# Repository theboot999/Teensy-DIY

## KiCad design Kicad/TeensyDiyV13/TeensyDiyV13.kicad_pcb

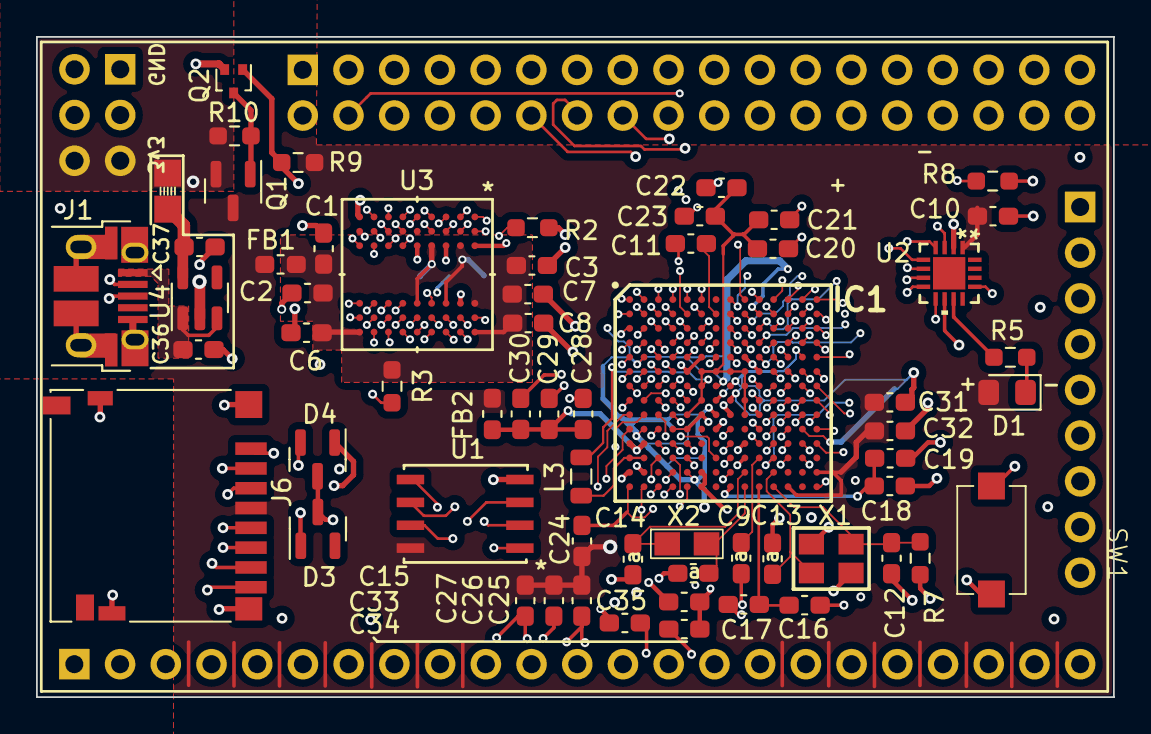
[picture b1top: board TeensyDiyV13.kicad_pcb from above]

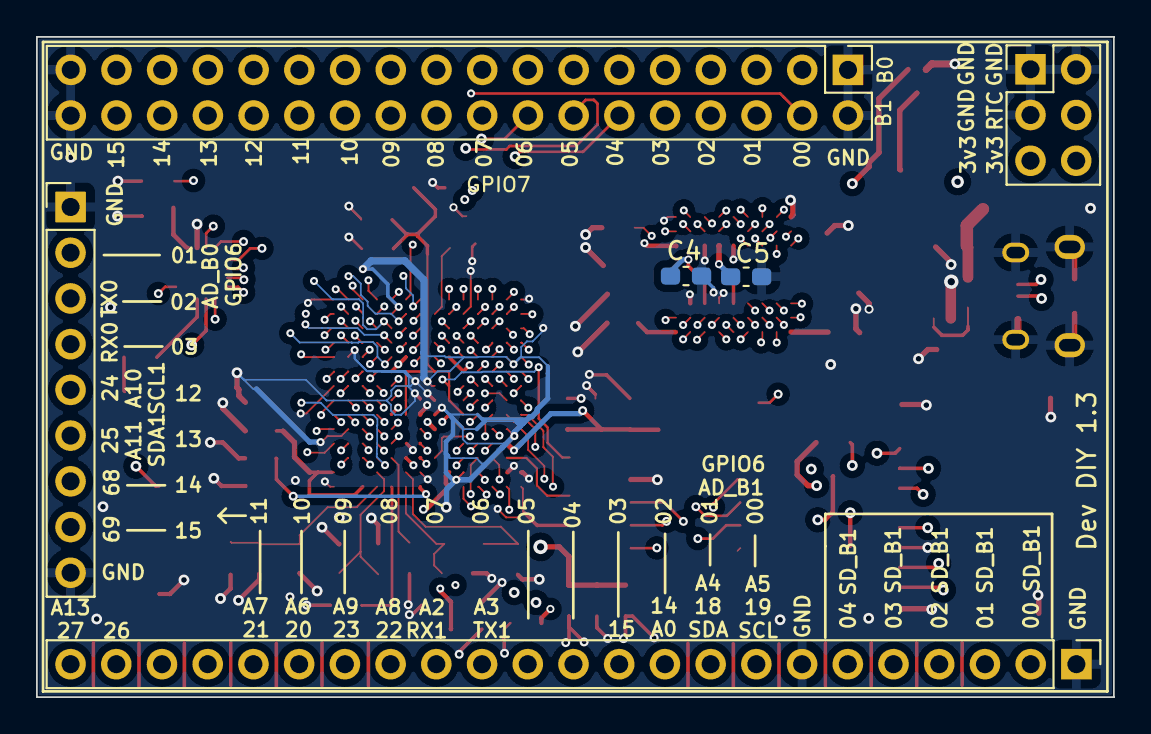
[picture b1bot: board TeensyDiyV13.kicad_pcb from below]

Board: 4 copper layers, 59.8 x 36.7 mm, 67 parts (6 on the bottom side), 146 nets.

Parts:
C1, C2, C3, C4, C5, C6, C7, C8, C9, C10, C11, C12, C13, C14, C15, C16, C17, C18, C19, C20, C21, C22, C23, C24, C25, C26, C27, C28, C29, C30, C31, C32, C33, C34, C35, C36, C37: C; C_0603_1608Metric_Pad1.08x0.95mm_HandSolder
D1: LED; LED_0805_2012Metric_Pad1.15x1.40mm_HandSolder
D3, D4: BAT54C; SOT-23
FB1, FB2: FerriteBead; L_0603_1608Metric_Pad1.05x0.95mm_HandSolder
IC1: MIMXRT1062DVJ6B; BGA196C80P14X14_1200X1200X152
J1: USB_B_Micro; USB_Micro-B_Amphenol_10103594-0001LF_Horizontal
J2: Conn_01x23; PinHeader_1x23_P2.54mm_Vertical
J3: Conn_02x18_Odd_Even; PinHeader_2x18_P2.54mm_Vertical
J4: Conn_01x08; PinHeader_1x09_P2.54mm_Vertical
J6: Micro_SD_Card_Det_Hirose_DM3AT; microSD_HC_Hirose_DM3D-SF
J7: Conn_02x04_Odd_Even; PinHeader_2x03_P2.54mm_Vertical
L3: L; L_0805_2012Metric
Q1: DMG2305UXQ; SOT-23
Q2: RE1C002UNTCL; SOT-416
R2, R3, R5, R7, R8, R9, R10: R; R_0603_1608Metric_Pad0.98x0.95mm_HandSolder
SW1: SW_Push; PTS636Button
U1: W25Q128JVPIM; Smaller_SOIC_128JVPIM_WIN
U2: MKL02Z32VFG4; QFN-16_3X3X0.65_NXP
U3: IS42S16160J-6BLI; TFBGA-54_8X8_ISI
U4: AP2112K-3.3; SOT-23-5
U5: Bridge
X1: TSX-3225
X2: Q13FC1350000400; XTAL_FC-135_EPS

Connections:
/3v3Vin: D4.1, IC1.N6 (USB_OTG1_VBUS), IC1.P6 (USB_OTG2_VBUS), J7.5, J7.6, Q1.2 (S), R10.2, U5.2 (OUT)
/3v3_Controlled: C10.2, C24.1, C25.1, C26.1, C27.1, C31.1, C32.1, D1.2 (A), FB1.2, FB2.1, IC1.E6 (NVCC_EMC_1), IC1.E9 (NVCC_GPIO_1), IC1.F5 (NVCC_EMC_2), IC1.F10 (NVCC_GPIO_2), IC1.J6 (NVCC_SD0), IC1.J10 (NVCC_GPIO_3), IC1.K4 (DCDC__IN_Q), IC1.K5 (NVCC_SD1), IC1.N14 (VDDA_ADC_3P3), IC1.P12 (VDD_HIGH_IN), J6.4 (VDD), Q1.3 (D), R9.2, U1.8 (VCC), U2.1 (VDD)
/AD_B0_01: IC1.H10 (GPIO_AD_B0_01), J4.2
/AD_B0_02: IC1.M11 (*GPIO_AD_B0_02), J4.3
/AD_B0_03: IC1.G11 (*GPIO_AD_B0_03), J4.4
/AD_B0_04: IC1.F11 (GPIO_AD_B0_04), U2.4 (PTA4)
/AD_B0_06: IC1.E14 (GPIO_AD_B0_06), U2.5 (PTA5)
/AD_B0_07: IC1.F12 (GPIO_AD_B0_07), U2.8 (PTB0)
/AD_B0_08: IC1.F13 (GPIO_AD_B0_08), U2.13 (PTB5)
/AD_B0_09: IC1.F14 (GPIO_AD_B0_09), U2.7 (PTA7)
/AD_B0_10: IC1.G13 (GPIO_AD_B0_10), U2.6 (PTA6)
/AD_B0_12: IC1.K14 (*GPIO_AD_B0_12), J4.5
/AD_B0_13: IC1.L14 (*GPIO_AD_B0_13), J4.6
/AD_B0_14: IC1.H14 (*GPIO_AD_B0_14), J4.7
/AD_B0_15: IC1.L10 (*GPIO_AD_B0_15), J4.8
/AD_B1_00: IC1.J11 (*GPIO_AD_B1_00), J2.8
/AD_B1_01: IC1.K11 (*GPIO_AD_B1_01), J2.9
/AD_B1_02: IC1.L11 (*GPIO_AD_B1_02), J2.10
/AD_B1_03: IC1.M12 (*GPIO_AD_B1_03), J2.11
/AD_B1_04: IC1.L12 (*GPIO_AD_B1_04), J2.12
/AD_B1_05: IC1.K12 (*GPIO_AD_B1_05), J2.13
/AD_B1_06: IC1.J12 (*GPIO_AD_B1_06), J2.14
/AD_B1_07: IC1.K10 (*GPIO_AD_B1_07), J2.15
/AD_B1_08: IC1.H13 (*GPIO_AD_B1_08), J2.16
/AD_B1_09: IC1.M13 (*GPIO_AD_B1_09), J2.17
/AD_B1_10: IC1.L13 (*GPIO_AD_B1_10), J2.18
/AD_B1_11: IC1.J13 (*GPIO_AD_B1_11), J2.19
/AD_B1_12: IC1.H12 (*GPIO_AD_B1_12), J2.20
/AD_B1_13: IC1.H11 (*GPIO_AD_B1_13), J2.21
/AD_B1_14: IC1.G12 (*GPIO_AD_B1_14), J2.22
/AD_B1_15: IC1.J14 (*GPIO_AD_B1_15), J2.23
/B0_00: IC1.D7 (GPIO_B0_00), J3.3
/B0_01: IC1.E7 (GPIO_B0_01), J3.5
/B0_02: IC1.E8 (GPIO_B0_02), J3.7
/B0_03: IC1.D8 (GPIO_B0_03), J3.9
/B0_04: IC1.C8 (GPIO_B0_04), J3.11
/B0_05: IC1.B8 (GPIO_B0_05), J3.13
/B0_06: IC1.A8 (GPIO_B0_06), J3.15
/B0_07: IC1.A9 (GPIO_B0_07), J3.17
/B0_08: IC1.B9 (GPIO_B0_08), J3.19
/B0_09: IC1.C9 (GPIO_B0_09), J3.21
/B0_10: IC1.D9 (GPIO_B0_10), J3.23
/B0_11: IC1.A10 (GPIO_B0_11), J3.25
/B0_12: IC1.C10 (GPIO_B0_12), J3.27
/B0_13: IC1.D10 (GPIO_B0_13), J3.29
/B0_14: IC1.E10 (GPIO_B0_14), J3.31
/B0_15: IC1.E11 (GPIO_B0_15), J3.33
/B1_00: IC1.A11 (GPIO_B1_00), J3.4
/B1_01: IC1.B11 (GPIO_B1_01), J3.6
/B1_02: IC1.C11 (GPIO_B1_02), J3.8
/B1_03: IC1.D11 (GPIO_B1_03), J3.10
/B1_04: IC1.E12 (GPIO_B1_04), J3.12
/B1_05: IC1.D12 (GPIO_B1_05), J3.14
/B1_06: IC1.C12 (GPIO_B1_06), J3.16
/B1_07: IC1.B12 (GPIO_B1_07), J3.18
/B1_08: IC1.A12 (GPIO_B1_08), J3.20
/B1_09: IC1.A13 (GPIO_B1_09), J3.22
/B1_10: IC1.B13 (GPIO_B1_10), J3.24
/B1_11: IC1.C13 (GPIO_B1_11), J3.26
/B1_12: IC1.D13 (GPIO_B1_12), J3.28
/B1_13: IC1.D14 (GPIO_B1_13), J3.30
/B1_14: IC1.C14 (GPIO_B1_14), J3.32
/B1_15: IC1.B14 (GPIO_B1_15), J3.34
/DCDC_PSWITCH: IC1.G10 (GPIO_AD_B0_11), IC1.K3 (DCDC_PSWITCH), R8.2, U2.3 (PTA3)
/EMC_00: IC1.E3 (GPIO_EMC_00), U3.A8 (DQ0)
/EMC_01: IC1.F3 (GPIO_EMC_01), U3.B9 (DQ1)
/EMC_02: IC1.F4 (GPIO_EMC_02), U3.B8 (DQ2)
/EMC_3: IC1.E4 (GPIO_EMC_37), U3.A2 (DQ15)
/EMC_03: IC1.G4 (GPIO_EMC_03), U3.C9 (DQ3)
/EMC_04: IC1.F2 (GPIO_EMC_04), U3.C8 (DQ4)
/EMC_05: IC1.G5 (GPIO_EMC_05), U3.D9 (DQ5)
/EMC_06: IC1.H5 (GPIO_EMC_06), U3.D8 (DQ6)
/EMC_07: IC1.H4 (GPIO_EMC_07), U3.E9 (DQ7)
/EMC_08: IC1.H3 (GPIO_EMC_08), U3.E8 (LDQM)
/EMC_09: IC1.C2 (GPIO_EMC_09), U3.H7 (AD_0)
/EMC_10: IC1.G1 (GPIO_EMC_10), U3.H8 (AD_1)
/EMC_11: IC1.G3 (GPIO_EMC_11), U3.J8 (AD_2)
/EMC_12: IC1.H1 (GPIO_EMC_12), U3.J7 (AD_3)
/EMC_13: IC1.A6 (GPIO_EMC_13), U3.J3 (AD_4)
/EMC_14: IC1.B6 (GPIO_EMC_14), U3.J2 (AD_5)
/EMC_15: IC1.B1 (GPIO_EMC_15), U3.H3 (AD_6)
/EMC_16: IC1.A5 (GPIO_EMC_16), U3.H2 (AD_7)
/EMC_17: IC1.A4 (GPIO_EMC_17), U3.H1 (AD_8)
/EMC_18: IC1.B2 (GPIO_EMC_18), U3.G3 (AD_9)
/EMC_19: IC1.B4 (GPIO_EMC_19), U3.G2 (AD_11)
/EMC_20: IC1.A3 (GPIO_EMC_20), U3.G1 (AD_12)
/EMC_21: IC1.C1 (GPIO_EMC_21), U3.G7 (B_A_0)
/EMC_22: IC1.F1 (GPIO_EMC_22), U3.G8 (B_A_1)
/EMC_23: IC1.G2 (GPIO_EMC_23), U3.H9 (AD_10)
/EMC_24: IC1.D3 (GPIO_EMC_24), U3.F7 (CAS)
/EMC_25: IC1.D2 (GPIO_EMC_25), U3.F8 (RAS)
/EMC_26: IC1.B3 (GPIO_EMC_26), U3.F2 (CLK)
/EMC_27: IC1.A2 (GPIO_EMC_27), R2.2, U3.F3 (CKE)
/EMC_28: IC1.D1 (GPIO_EMC_28), U3.F9 (WE)
/EMC_29: IC1.E1 (GPIO_EMC_29), R3.2, U3.G9 (CS)
/EMC_30: IC1.C6 (GPIO_EMC_30), U3.E1 (DQ8)
/EMC_31: IC1.C5 (GPIO_EMC_31), U3.D2 (DQ9)
/EMC_32: IC1.D5 (GPIO_EMC_32), U3.D1 (DQ10)
/EMC_33: IC1.C4 (GPIO_EMC_33), U3.C2 (DQ11)
/EMC_34: IC1.D4 (GPIO_EMC_34), U3.C1 (DQ12)
/EMC_35: IC1.E5 (GPIO_EMC_35), U3.B2 (DQ13)
/EMC_36: IC1.C3 (GPIO_EMC_36), U3.B1 (DQ14)
/EMC_38: IC1.D6 (GPIO_EMC_38), U3.F1 (UDQM)
/GND: C1.1, C2.1, C3.1, C4.1, C5.1, C6.1, C7.1, C8.1, C9.1, C10.1, C11.1, C12.1, C13.2, C14.2, C15.2, C16.1, C17.1, C18.1, C19.1, C20.2, C21.2, C22.2, C23.2, C24.2, C25.2, C26.2, C27.2, C28.2, C29.2, C30.2, C31.2, C32.2, C33.2, C34.2, C35.2, C36.2, C37.2, IC1.A1 (VSS_1), IC1.A14 (VSS_2), IC1.B5 (VSS_3), IC1.B10 (VSS_4), IC1.E2 (VSS_5), IC1.E13 (VSS_6), IC1.G7 (VSS_7), IC1.G8 (VSS_8), IC1.G14 (GPIO_AD_B0_05), IC1.H7 (VSS_9), IC1.H8 (VSS_10), IC1.J7 (VSS_11), IC1.J8 (VSS_12), IC1.K2 (VSS_13), IC1.K13 (VSS_14), IC1.L9 (VSS_15), IC1.N1 (DCDC_GND_1), IC1.N2 (DCDC_GND_2), IC1.N5 (VSS_16), IC1.N8 (VSS_17), IC1.P1 (VSS_18), IC1.P14 (VSS_19), J1.5 (GND), J1.6 (Shield), J2.1, J2.7, J3.1, J3.2, J3.35, J3.36, J4.1, J4.9, J6.6 (VSS), J6.11 (SHIELD), J7.1, J7.2, J7.3, Q2.2 (S), R2.1, R7.1, R8.1, SW1.2, U1.4 (GND), U2.2 (VSS), U3.A1 (VSS1), U3.A3 (VSSQ1), U3.B7 (VSSQ2), U3.C3 (VSSQ3), U3.D7 (VSSQ4), U3.E3 (VSS2), U3.J1 (VSS3), U4.2 (GND), X1.2, X1.4
/PMIC: IC1.K7 (PMIC_ON_REQ), Q2.1 (G), R9.1
/PROG_SWITCH: SW1.1, U2.10 (PTB2)
/SD_B0_00: IC1.J4 (GPIO_SD_B0_00), J6.3 (CMD)
/SD_B0_01: IC1.J3 (GPIO_SD_B0_01), J6.5 (CLK)
/SD_B0_02: IC1.J1 (GPIO_SD_B0_02), J6.7 (DAT0)
/SD_B0_03: IC1.K1 (GPIO_SD_B0_03), J6.8 (DAT1)
/SD_B0_04: IC1.H2 (GPIO_SD_B0_04), J6.1 (DAT2)
/SD_B0_05: IC1.J2 (GPIO_SD_B0_05), J6.2 (DAT3/CD)
/SD_B1_00: IC1.L5 (GPIO_SD_B1_00), J2.2
/SD_B1_01: IC1.M5 (GPIO_SD_B1_01), J2.3
/SD_B1_02: IC1.M3 (GPIO_SD_B1_02), J2.4
/SD_B1_03: IC1.M4 (GPIO_SD_B1_03), J2.5
/SD_B1_04: IC1.P2 (GPIO_SD_B1_04), J2.6
/SD_B1_06: IC1.L3 (GPIO_SD_B1_06), U1.1 (CS)
/SD_B1_07: IC1.L4 (GPIO_SD_B1_07), U1.6 (CLK)
/SD_B1_08: IC1.P3 (GPIO_SD_B1_08), U1.5 (D0)
/SD_B1_09: IC1.N4 (GPIO_SD_B1_09), U1.2 (D1)
/SD_B1_10: IC1.P4 (GPIO_SD_B1_10), U1.3 (D2)
/SD_B1_11: IC1.P5 (GPIO_SD_B1_11), U1.7 (D3)
/SD_RAM_3v3: C1.2, C2.2, C3.2, C4.2, C5.2, C6.2, C7.2, C8.2, FB1.1, R3.1, U3.A7 (VDDQ1), U3.A9 (VDD1), U3.B3 (VDDQ2), U3.C7 (VDDQ3), U3.D3 (VDDQ4), U3.E7 (VDD2), U3.J9 (VDD3)
/USB1DN: IC1.M8 (USB_OTG1_DN), J1.2 (D-)
/USB1DP: IC1.L8 (USB_OTG1_DP), J1.3 (D+)
/USB+: C36.1, J1.1 (VBUS), U4.1 (VIN), U4.3 (EN)
/VBat: D4.2, J7.4
unnamed: D1.1 (K), R5.1
unnamed: C28.1, C29.1, C30.1, FB2.2, IC1.L1 (DCDC_IN_1), IC1.L2 (DCDC_IN_2)
unnamed: IC1.M1 (DCDC_LP_1), IC1.M2 (DCDC_LP_2), L3.2
unnamed: C20.1, C21.1, C22.1, C23.1, IC1.F6 (VDD_SOC_IN_1), IC1.F7 (VDD_SOC_IN_2), IC1.F8 (VDD_SOC_IN_3), IC1.F9 (VDD_SOC_IN_4), IC1.G6 (VDD_SOC_IN_5), IC1.G9 (VDD_SOC_IN_6), IC1.H6 (VDD_SOC_IN_7), IC1.H9 (VDD_SOC_IN_8), IC1.J5 (DCDC_SENSE), IC1.J9 (VDD_SOC_IN_9), L3.1
unnamed: C11.2, IC1.B7 (GPIO_EMC_39)
unnamed: C16.2, C17.2, IC1.P10 (NVCC_PLL)
unnamed: IC1.M7 (POR_B), U2.9 (PTB1)
unnamed: C14.1, IC1.N9 (RTC_XTALI), X2.1
unnamed: C15.1, IC1.P9 (RTC_XTALO), X2.2
unnamed: C18.2, C19.2, IC1.P8 (VDD_HIGH_CAP)
unnamed: C9.2, IC1.M10 (VDD_SNVS_CAP)
unnamed: C35.1, D3.3, D4.3, IC1.M9 (VDD_SNVS_IN)
unnamed: C33.1, C34.1, D3.1, IC1.K8 (VDD_USB_CAP)
unnamed: C12.2, IC1.P11 (XTALI), R7.2, X1.3
unnamed: C13.1, IC1.N11 (XTALO), X1.1
unnamed: Q1.1 (G), Q2.3 (D), R10.1
unnamed: R5.2, U2.11 (PTB3)
unnamed: C37.1, U4.5 (VOUT), U5.1 (IN)

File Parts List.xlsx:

Qty | Description | Product | Package Size | Designator | Link
1 | Microcontroller 12x12 | MIMXRT1062DVJ6B_BGA196 | BGC 12x12 | IC1 | https://au.mouser.com/ProductDetail/NXP-Semiconductors/MIMXR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
1 | Flash Memory 128 mB | W25Q128JVPIM | WSON-8 | U1 | https://au.mouser.com/ProductDetail/Winbond/W25Q128JVPIM?qs=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
1 | Boot Loader | MKL02Z32_T4_QFN16 | QFN-16 | U2 | https://www.pjrc.com/store/ic_mkl02_t4.html
1 | Ram Chip | IS42S16160J-6BLI | BGA-54 | U3 | https://au.mouser.com/ProductDetail/ISSI/IS42S16160J-6BLI?qs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
1 | P Channel Mosfet | DMG2305UXQ-7 | SOT-23-3 | Q1 | https://www.mouser.com/ProductDetail/Diodes-Incorporated/DMG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
1 | N Channel Mosfet | RE1C002UNTCL | SOT-416 | Q2 | https://au.mouser.com/ProductDetail/ROHM-Semiconductor/RE1C0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
1 | USB-B Micro | 10103594-0001LF |  | J1 | https://au.mouser.com/ProductDetail/Amphenol-FCI/10103594-00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
1 | Clock 32.768khz | Q13FC1350000400 | 3.2 mm x 1.5 mm | X2 | https://au.mouser.com/ProductDetail/Epson-Timing/FC-135-32.7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
1 | Clock 24mhz | TSX-3225 24.0000MF20G-AC0 | 3.2 mm x 2.5 mm | X1 | https://au.mouser.com/ProductDetail/Epson-Timing/TSX-3225-24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
2 | BAT54C Shottky Diode | BAT54C/SOT23/TO-236AB | SOT-23-3 | D3, D4 | https://au.mouser.com/ProductDetail/Nexperia/BAT54C215?qs=me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
1 | SD CARD | DM3D-SF(41) |  | J6 | https://au.mouser.com/ProductDetail/Hirose-Connector/DM3D-SF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
1 | Button | PTS636SKG25JSMTR LFS |  | SW1 | https://au.mouser.com/ProductDetail/CK/PTS636SKG25JSMTR-LFS?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
1 | 3.3V Regulator | AP2112K-3.3TRG1 | SOT-25-5 | U4 | https://au.mouser.com/ProductDetail/Diodes-Incorporated/AP21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
2 | Ferrite Bead 0603 120Ω | MH1608-121Y | 603 | FB1, FB2 | https://www.mouser.com/ProductDetail/Bourns/MH1608-121Y?qs=s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
1 | Inductor 0805 4.7UH | LQM21PN4R7MGRD | 805 | L3 | https://au.mouser.com/ProductDetail/Murata-Electronics/LQM21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
1 | Led 0805 Red | SML-LX0805IC-TR | 805 | D1 | https://au.mouser.com/ProductDetail/Lumex/SML-LX0805IC-TR?qs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
6 | 100k Resistor 0603 | ERA-3AED104V | 603 | R1, R2, R3, R7, R8, R9, R10 | https://au.mouser.com/ProductDetail/Panasonic/ERA-3AED104V?q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
1 | 1k Resistor 0603 | CRCW06031K00FKED | 603 | R5 | https://au.mouser.com/ProductDetail/Vishay-Dale/CRCW06031K00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
1 | 2.2M Resistor 0603 | RK73H1JRTTD2204F | 603 | R7 | https://au.mouser.com/ProductDetail/KOA-Speer/RK73H1JRTTD220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
6 | 0.1uf Capacitor 0603 | KGM15AR71A104KT | 603 | C3, C4, C5, C6, C7, C8 | https://au.mouser.com/ProductDetail/KYOCERA-AVX/KGM15AR71A10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
6 | 4.7uf Capacitor 0603 | LMK107BJ475KA-T | 603 | C2, C17, C19, C22, C26, C29 | https://au.mouser.com/ProductDetail/TAIYO-YUDEN/LMK107BJ475K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
5 | 10pf Capacitor 0603 | VJ0603A100FXQPW1BC | 603 | C11, C12, C13, C14, C15 | https://au.mouser.com/ProductDetail/Vishay-Vitramon/VJ0603A1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
1 | 22uf Capacitor 0603 | KAM15CT70J226KT | 603 | C1 | https://au.mouser.com/ProductDetail/KYOCERA-AVX/KAM15CT70J22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
10 | 0.22uf Capacitor 0603 | GRM188R71A224KA01J | 603 | C9,C10,C16,C18,C21,C25,C28,C32,C33,C35 | https://au.mouser.com/ProductDetail/Murata-Electronics/GRM18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
2 | 0.01uf Capacitor 0603 | 885012206014 | 603 | C20, C24 | https://au.mouser.com/ProductDetail/Wurth-Elektronik/8850122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
2 | 10uf Capacitor 0603 | GRM188R61A106ME69D | 603 | C30,C23,C34 | https://au.mouser.com/ProductDetail/Murata-Electronics/GRM18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
4 | 2.2uf Capacitor 0603 | LMK107B7225KA-TR | 603 | C27,C31,C36,C37 | https://au.mouser.com/ProductDetail/TAIYO-YUDEN/LMK107B7225K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

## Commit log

2025-04-29 Create a

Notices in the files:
parts and their libraries:
COPYRIGHT: Copyright (C) 2023 Ultra Librarian. All rights reserved.
